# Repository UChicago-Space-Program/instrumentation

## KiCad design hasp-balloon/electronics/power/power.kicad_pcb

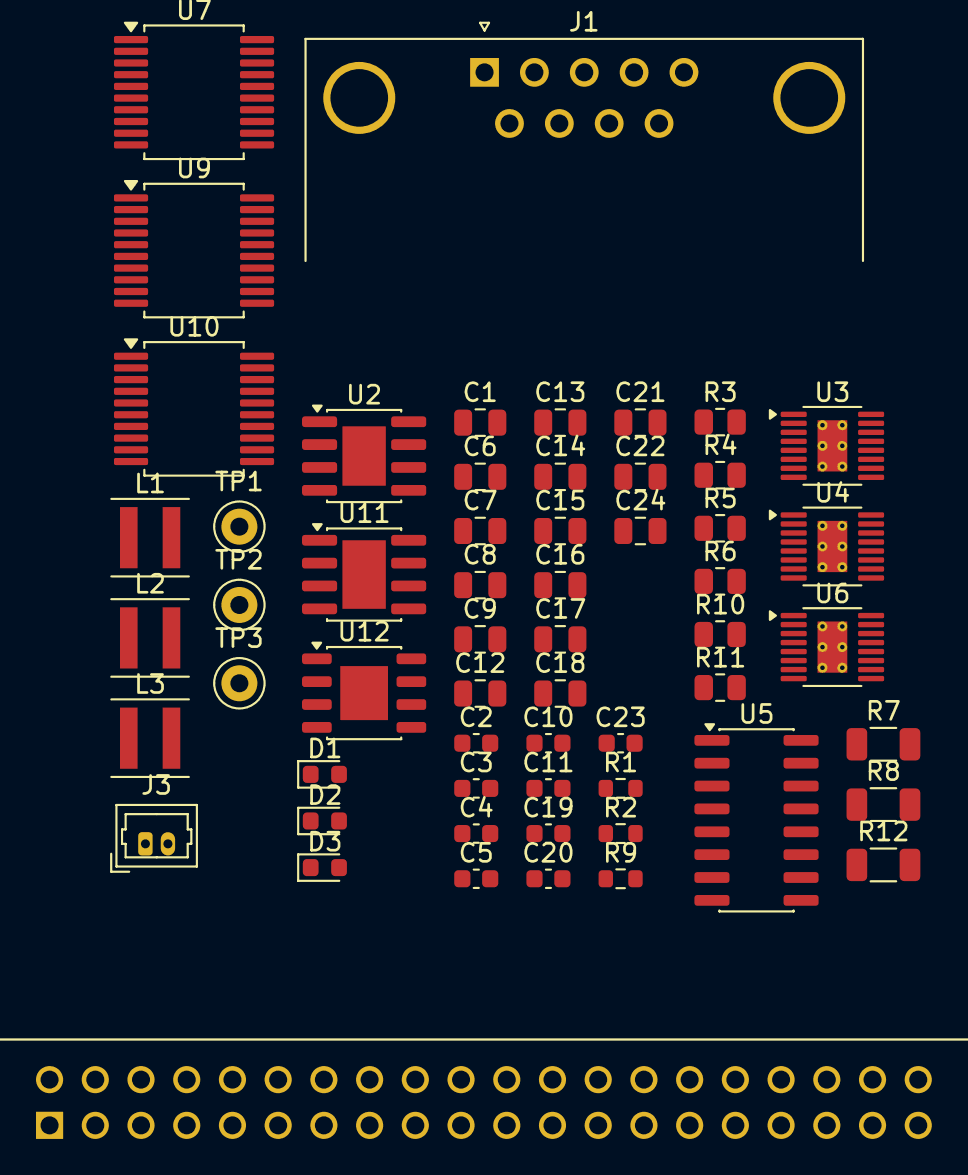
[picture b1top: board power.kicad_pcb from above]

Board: 2 copper layers, 58 parts (0 on the bottom side), 44 nets, no tracks yet.

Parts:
C1, C8, C9, C14, C15, C16, C17, C18, C22: 0.1uF; C_0805_2012Metric
C2, C3, C19: 10nF; C_0603_1608Metric
C4, C5, C20: 4.7uF; C_0603_1608Metric
C6, C7, C21: 10pF; C_0805_2012Metric
C10, C11, C23: 1uF; C_0603_1608Metric
C12, C13, C24: 68uF; C_0805_2012Metric
D1, D2, D3: 150060VS75000; LED_0603_1608Metric
J1: DB9; DSUB-9_Pins_Horizontal_P2.77x2.84mm_EdgePinOffset7.70mm_Hou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
J3: Screw Terminal 1x2; Molex_PicoBlade_53047-0210_1x02_P1.25mm_Vertical
L1, L2, L3: 10uH; L_Coilcraft_XxL4040
R1, R2, R9: 110k; R_0603_1608Metric
R3, R4, R10: 243k; R_0805_2012Metric
R5, R6, R11: 1M; R_0805_2012Metric
R7, R8, R12: 150; C_1206_3216Metric
TP1, TP2, TP3: TestPoint_Keystone_5000-5004_Miniature
U1: RASPBERRY_PI_ZERO_2_W; MODULE_RASPBERRY_PI_ZERO_2_W
U2: TMP36FSZ; SOIC-8-1EP_3.9x4.9mm_P1.27mm_EP2.41x3.3mm
U3, U4, U6: LT8610; MSOP-16-1EP_3x4.039mm_P0.5mm_EP1.651x2.845mm_ThermalVias
U5: MAX3232; SOIC-16_3.9x9.9mm_P1.27mm
U7, U9, U10: MAX31865xAP; SSOP-20_5.3x7.2mm_P0.65mm
U11: MCP3201; SOIC-8-1EP_3.9x4.9mm_P1.27mm_EP2.41x3.81mm
U12: BSP742T; Infineon_PG-DSO-8-27_3.9x4.9mm_EP2.65x3mm

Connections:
3V3: C1.2, C14.2, U1.1 (3V3_1), U1.17 (3V3_17), U2.5 (SHUTDOWN), U2.8 (V_IN), U5.16 (VCC)
5V: C6.2, C12.2, D1.2 (A), L1.2, R5.2, TP1.1, U1.2 (5V_2), U1.4 (5V_4), U3.14 (BIAS)
5V_STAT: U3.15 (PG), U4.15 (PG), U6.15 (PG)
6V: C7.2, C13.2, D2.2 (A), L2.2, R6.2, TP2.1, U4.14 (BIAS)
12V: C21.2, C24.2, D3.2 (A), L3.2, R11.2, TP3.1, U6.14 (BIAS), U12.5 (Vbb), U12.6 (Vbb), U12.7 (Vbb), U12.8 (Vbb)
28V: C4.1, U3.4 (EN/UV), U3.5 (VIN), U3.6 (VIN)
/FB_3: C6.1, C7.1, C21.1, R3.2, R4.2, R5.1, R6.1, R10.2, R11.1, U3.16 (FB), U4.16 (FB), U6.16 (FB)
/MISO: U1.21 (GPIO9/SPI_MISO), U7.17 (SDO), U9.17 (SDO), U10.17 (SDO)
/MOSI: U1.19 (GPIO10/SPI_MOSI), U7.14 (SDI), U9.14 (SDI), U10.14 (SDI)
/RS232_RX: J1.3, U5.13 (R1IN)
/RS232_TX: J1.2, U5.14 (T1OUT)
/SCLK: U1.23 (GPIO11/SPI_SCLK), U7.15 (SCLK), U9.15 (SCLK), U10.15 (SCLK)
/SW_3: C8.2, C9.2, C22.2, L1.1, L2.1, L3.1, U3.9 (SW), U3.10 (SW), U3.11 (SW), U4.9 (SW), U4.10 (SW), U4.11 (SW), U6.9 (SW), U6.10 (SW), U6.11 (SW)
/UART_RX: U1.10 (GPIO15/RXD0), U5.12 (R1OUT)
/UART_TX: U1.8 (GPIO14/TXD0), U5.11 (T1IN)
/VAC_EN: U1.40 (GPIO21), U12.2 (IN)
GND: C1.1, C2.1, C3.1, C4.2, C5.2, C10.2, C11.2, C12.1, C13.1, C14.1, C17.1, C18.1, C19.1, C20.2, C23.2, C24.1, J1.5, J3.2, R1.2, R2.2, R3.1, R4.1, R7.1, R8.1, R9.2, R10.1, R12.1, U1.6 (GND_6), U1.9 (GND_9), U1.14 (GND_14), U1.20 (GND_20), U1.25 (GND_25), U1.30 (GND_30), U1.34 (GND_34), U1.39 (GND_39), U2.4 (GND), U3.7 (GND), U3.8 (GND), U3.17 (GND), U4.7 (GND), U4.8 (GND), U4.17 (GND), U5.15 (GND), U6.7 (GND), U6.8 (GND), U6.17 (GND), U11.3 (IN-), U12.1 (GND)
unnamed: D1.1 (K), R7.2
unnamed: D2.1 (K), R8.2
unnamed: D3.1 (K), R12.2
unnamed: J3.1, U12.3 (OUT)
unnamed: C8.1, U3.12 (BST)
unnamed: C10.1, U3.13 (INTVcc)
unnamed: R1.1, U3.3 (RT)
unnamed: C2.2, U3.2 (TR/SS)
unnamed: C9.1, U4.12 (BST)
unnamed: C11.1, U4.13 (INTVcc)
unnamed: R2.1, U4.3 (RT)
unnamed: C3.2, U4.2 (TR/SS)
unnamed: C15.2, U5.1 (C1+)
unnamed: C15.1, U5.3 (C1-)
unnamed: C16.1, U5.4 (C2+)
unnamed: C16.2, U5.5 (C2-)
unnamed: C17.2, U5.2 (VS+)
unnamed: C18.2, U5.6 (VS-)
unnamed: C22.1, U6.12 (BST)
unnamed: C23.1, U6.13 (INTVcc)
unnamed: R9.1, U6.3 (RT)
unnamed: C19.2, U6.2 (TR/SS)
unnamed: U7.13 (GND), U7.19 (GND)
unnamed: U9.13 (GND), U9.19 (GND)
unnamed: U10.13 (GND), U10.19 (GND)
unnamed: U2.1 (V_OUT), U11.2 (IN+)
VBATT: C5.1, C20.1, U4.4 (EN/UV), U4.5 (VIN), U4.6 (VIN), U6.4 (EN/UV), U6.5 (VIN), U6.6 (VIN)

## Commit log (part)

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2025-11-01 feat: initialize
2025-11-01 feat: power board
2025-11-04 feat: schematic v1
2025-11-05 add HASP proposal
2026-05-23 feat: scripts for sensors
